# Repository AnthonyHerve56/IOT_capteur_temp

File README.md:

# IOT_capteur_temp
Création d'un capteur de température sur kicad pour le cours de IOT

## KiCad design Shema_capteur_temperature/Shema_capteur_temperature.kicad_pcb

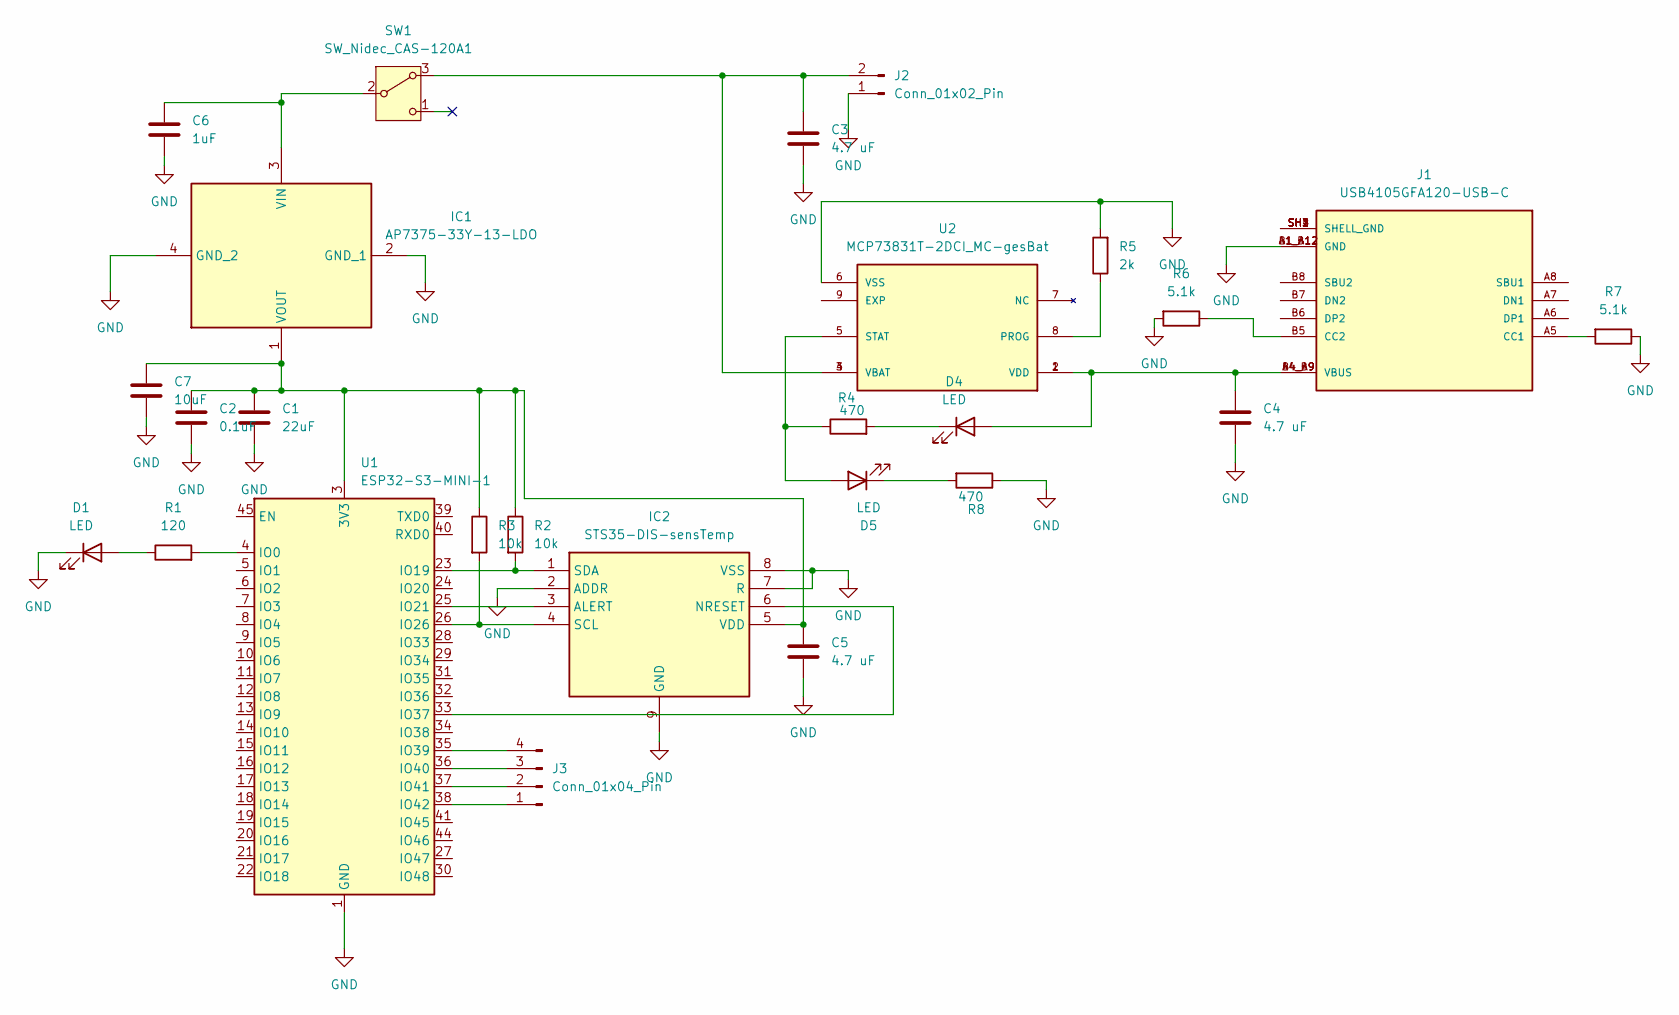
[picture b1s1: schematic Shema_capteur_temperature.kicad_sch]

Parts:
C1: 22uF; C_0402_1005Metric
C2: 0.1uF; C_0402_1005Metric
C3, C4, C5: 4.7 uF; C_0402_1005Metric
C6: 1uF; C_0402_1005Metric
C7: 10uF; C_0402_1005Metric
D1, D4, D5: LED; LED_0603_1608Metric
IC1: AP7375-33Y-13-LDO; BCX53TA; Manufacturer_Part_Number AP7375-33Y-13; Mouser Part Number 621-AP7375-33Y-13
IC2: STS35-DIS-sensTemp; STS35-DIS; Manufacturer_Part_Number STS35-DIS; Mouser Part Number 403-STS35-DIS
J1: USB4105GFA120-USB-C; GCT_USB4105GFA120; PARTREV B3
J2: Conn_01x02_Pin; PinHeader_1x02_P2.54mm_Vertical
J3: Conn_01x04_Pin; PinHeader_1x04_P2.54mm_Vertical
R1: 120; LED_0603_1608Metric
R2, R3: 10k; LED_0603_1608Metric
R4, R8: 470; LED_0603_1608Metric
R5: 2k; LED_0603_1608Metric
R6, R7: 5.1k; LED_0603_1608Metric
SW1: SW_Nidec_CAS-120A1; Nidec_Copal_CAS-120A
U1: ESP32-S3-MINI-1; ESP32-S2-MINI-1
U2: MCP73831T-2DCI_MC-gesBat; MCP73831T-2DCI_MC; PARTREV H

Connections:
GND: C1.2, C2.2, C3.2, C4.2, C5.2, C6.2, C7.2, D1.1 (K), IC1.2 (GND_1), IC1.4 (GND_2), IC2.2 (ADDR), IC2.7 (R), IC2.8 (VSS), IC2.9 (GND), J1.A1_B12 (GND), J1.B1_A12 (GND), J2.1, R5.2, R6.2, R7.1, R8.1, U1.1 (GND), U1.2 (GND), U1.42 (GND), U1.43 (GND), U1.46 (GND), U1.47 (GND), U1.48 (GND), U1.49 (GND), U1.50 (GND), U1.51 (GND), U1.52 (GND), U1.53 (GND), U1.54 (GND), U1.55 (GND), U1.56 (GND), U1.57 (GND), U1.58 (GND), U1.59 (GND), U1.60 (GND), U1.61 (GND), U1.62 (GND), U1.63 (GND), U1.64 (GND), U1.65 (GND), U2.6 (VSS)
unnamed: D1.2 (A), R1.1
unnamed: C4.1, D4.2 (A), J1.A4_B9 (VBUS), J1.B4_A9 (VBUS), U2.1 (VDD), U2.2 (VDD)
unnamed: D4.1 (K), R4.2
unnamed: D5.2 (A), R4.1, U2.5 (STAT)
unnamed: D5.1 (K), R8.2
unnamed: C6.1, IC1.3 (VIN), SW1.2 (B)
unnamed: C1.1, C2.1, C5.1, C7.1, IC1.1 (VOUT), IC2.5 (VDD), R2.1, R3.1, U1.3 (3V3)
unnamed: IC2.3 (ALERT), U1.25 (IO21)
unnamed: IC2.6 (NRESET), U1.33 (IO37)
unnamed: IC2.4 (SCL), R3.2, U1.26 (IO26)
unnamed: IC2.1 (SDA), R2.2, U1.23 (IO19)
unnamed: J1.A5 (CC1), R7.2
unnamed: J1.B5 (CC2), R6.1
unnamed: J1.SH1 (SHELL_GND), J1.SH2 (SHELL_GND), J1.SH3 (SHELL_GND), J1.SH4 (SHELL_GND)
unnamed: C3.1, J2.2, SW1.3 (A), U2.3 (VBAT), U2.4 (VBAT)
unnamed: J3.1, U1.38 (IO42)
unnamed: J3.2, U1.37 (IO41)
unnamed: J3.3, U1.36 (IO40)
unnamed: J3.4, U1.35 (IO39)
unnamed: R1.2, U1.4 (IO0)
unnamed: R5.1, U2.8 (PROG)

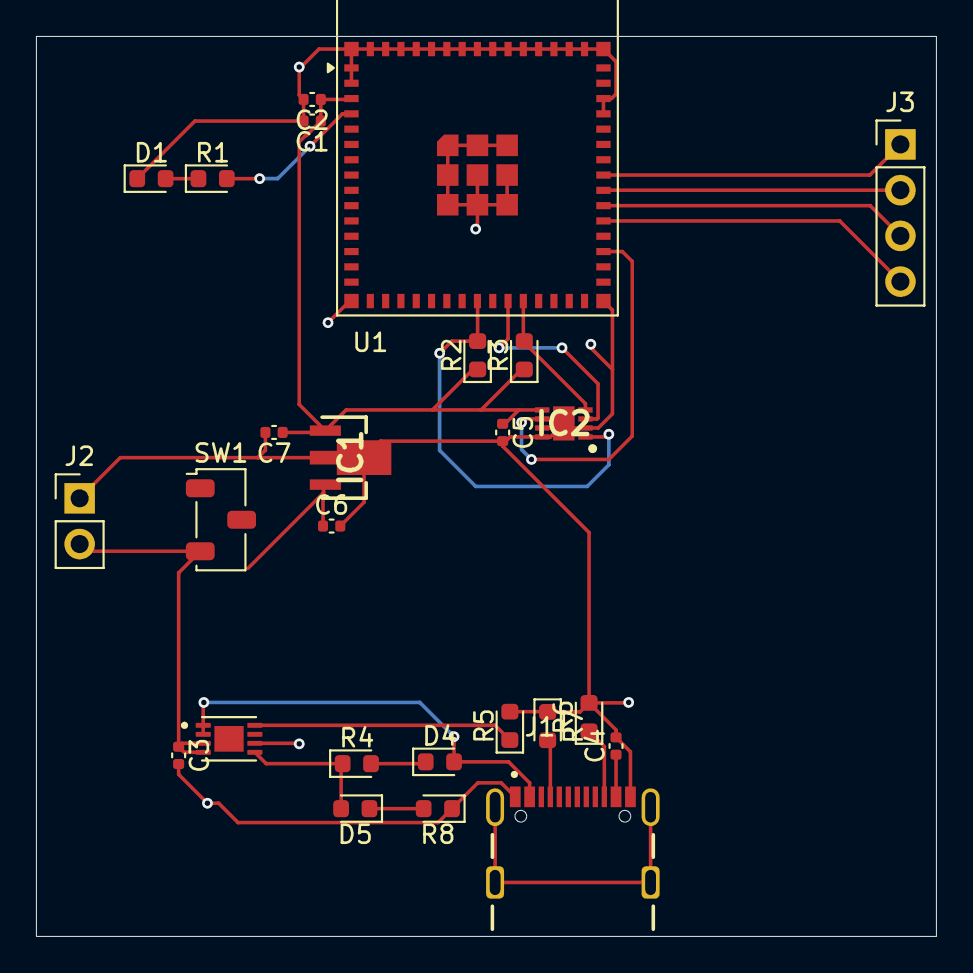
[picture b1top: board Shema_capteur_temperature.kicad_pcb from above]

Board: 2 copper layers, 50.0 x 50.0 mm, 26 parts (0 on the bottom side), 22 nets.

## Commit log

2024-10-24 Commit schéma
2024-10-24 Routage_PCB_Shaiek
